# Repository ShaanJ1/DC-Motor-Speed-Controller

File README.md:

# DC-Motor-Speed-Controller
A PWM speed controller made for the 775 DC Motor, but can be used with other motors as well. It features on/off buttons, an indicator LED, and a potentiometer to control the motor's speed

I made this as Version 2 of my motor controller for my V8 Engine project, as that board failed to work entirely because of bad design.

# Bill of Materials (BOM)

| **Item Name/Purpose** | **Product Number** | **URL** | **Price** | **Quantity** | **Designator** | **Note** |
| --------------------- | ------------------ | ------- | --------: | -----------: | -------------- | -------- |
| PCB | | https://jlcpcb.com/ | $3.50 | 5 | | |
| P Channel MOSFET | SI2323CDS-T1-BE3 | https://www.digikey.com/en/products/detail/vishay-siliconix/SI2323CDS-T1-BE3/16397482 | $1.21 | 1 | Q4 | |
| Zener Diode | MMSZ5V6T1G | https://www.digikey.ca/en/products/detail/onsemi/MMSZ5V6T1G/1749053 | $0.17 | 1 | D1 | |
| NPN Transistor | MMBT2222A-TP | https://www.digikey.ca/en/products/detail/mcc-micro-commercial-components/MMBT2222A-TP/717279 | $0.24 | 2 | Q3, Q6 | |
| 6A 2920 PTC Fuse | 2920L600/16MR | https://www.digikey.ca/en/products/detail/littelfuse-inc/2920L600-16MR/14320022 | $2.20 | 2 | F1 | |
| Flywheeling Diode | MBR2045CT | https://www.digikey.ca/en/products/detail/taiwan-semiconductor-corporation/MBR2045CT/7357796 | $1.72 | 1 | D3 | |
| N Channel MOSFET | IRF3205STRLPBF | https://www.digikey.ca/en/products/detail/infineon-technologies/IRF3205STRLPBF/856540 | $3.00 | 1 | Q5 | |
| Diode | 1N4148W-13-F | https://www.digikey.ca/en/products/detail/diodes-incorporated/1N4148W-13-F/1933928 | $0.36 | 2 | D5, D6 | |
| 0.01uF 0603 Capacitor | 06035C103MAZ2A | https://www.digikey.ca/en/products/detail/kyocera-avx/06035C103MAZ2A/11250083 | $0.12 | 1 | C2 | |
| 0.1uF 0704 C0G/NP0 Capacitor | GRMJN65C1H104JE01D | https://www.digikey.ca/en/products/detail/murata-electronics/GRMJN65C1H104JE01D/19115560 | $0.37 | 1 | C1 | |
| 555 Timer | LMC555 | https://www.digikey.ca/en/products/detail/texas-instruments/LMC555CMX-NOPB/334874 | $1.15 | 1 | U1 | |
| 10k 0603 Resistor | RC0603FR-0710KL | https://www.digikey.ca/en/products/detail/yageo/RC0603FR-0710KL/726880 | $0.25 | 10 | R1, R5, R6, R8, R11 | Cheaper to get 10 resistors than only 5 |
| 4.7K 0603 Resistor | RMCF0603FT4K70 | https://www.digikey.ca/en/products/detail/stackpole-electronics-inc/RMCF0603FT4K70/1760998 | $0.10 | 1 | R2 | |
| 1K 0603 Resistor | RMCF0603FT1K00 | https://www.digikey.ca/en/products/detail/stackpole-electronics-inc/RMCF0603FT1K00/1761077 | $0.21 | 10 | R3, R4, R7, R9, R10 | Cheaper to get 10 resistors than only 5 |
| 0805 SMD LED | LTST-C171KGKT | https://www.digikey.ca/en/products/detail/liteon/LTST-C171KGKT/386799 | $0.12 | 1 | D4 | |
| 1x2 Screw Terminals | 282837-2 | https://www.digikey.ca/en/products/detail/te-connectivity-amp-connectors/282837-2/2187973 | $3.44 | 2 | J1, M1 | |

#### <ins>Totals (not including taxes or shipping)</ins>

**Total (CAD):** $17.72

**Total (USD):** $12.57

### Images
Schematic

PCB

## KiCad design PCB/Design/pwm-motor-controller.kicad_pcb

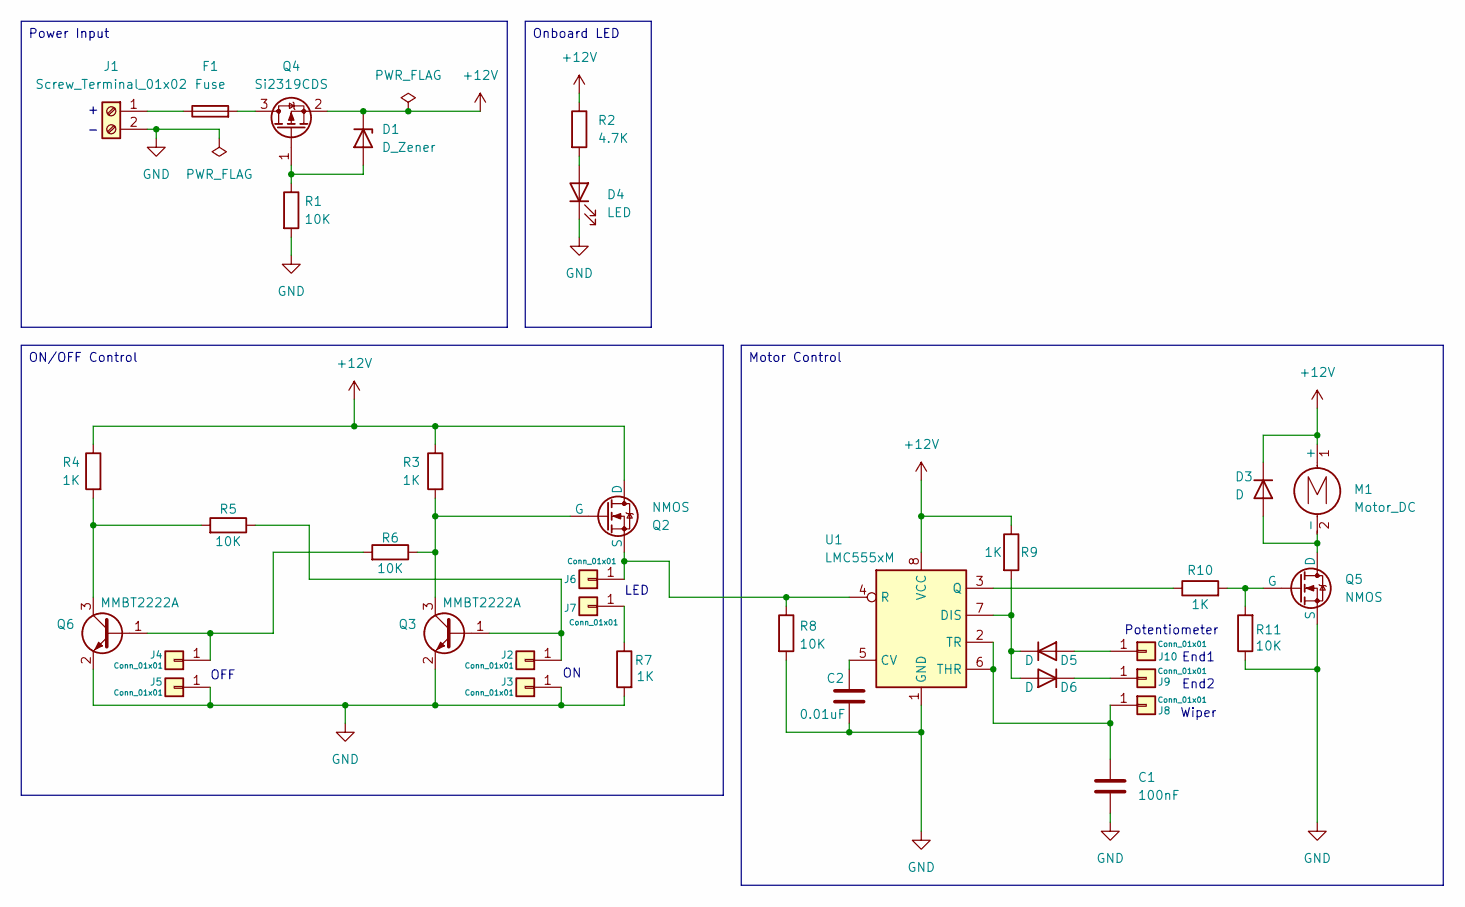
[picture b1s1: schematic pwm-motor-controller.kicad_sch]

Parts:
C1: 100nF; GRMJN65C1H104JE01D
C2: 0.01uF; C_0603_1608Metric
D1: D_Zener; D_SOD-123
D3: D; TO-220-3_Horizontal_TabDown
D4: LED; LED_0805_2012Metric_Pad1.15x1.40mm_HandSolder
D5, D6: D; Nexperia_CFP3_SOD-123W
F1: Fuse; Fuse_2920_7451Metric
J1: Screw_Terminal_01x02; TerminalBlock_Phoenix_MKDS-1,5-2-5.08_1x02_P5.08mm_Horizont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
J2, J3, J4, J5, J6, J7, J8, J9, J10: Conn_01x01; TestPoint_THTPad_2.0x2.0mm_Drill1.0mm
M1: Motor_DC; TerminalBlock_Phoenix_MKDS-1,5-2-5.08_1x02_P5.08mm_Horizont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
Q2: NMOS; SOT-23
Q3, Q6: MMBT2222A; SOT-23
Q4: Si2319CDS; SOT-23
Q5: NMOS; TO-263-2
R1, R5, R6, R8, R11: 10K; R_0603_1608Metric
R2: 4.7K; R_0603_1608Metric
R3, R4, R7, R9, R10: 1K; R_0603_1608Metric
U1: LMC555xM; SOIC-8_3.9x4.9mm_P1.27mm

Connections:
+12V: D1.1 (K), D3.1 (K), M1.1 (+), Q2.1 (D), Q4.2 (S), R2.1, R3.1, R4.1, R9.1, U1.8 (VCC)
GND: C1.2, C2.1, D4.1 (K), J1.2, J3.1, J5.1, Q3.2 (E), Q5.3 (S), Q6.2 (E), R1.2, R7.2, R8.2, R11.1, U1.1 (GND)
unnamed: D1.2 (A), Q4.1 (G), R1.1
unnamed: D3.2 (A), M1.2 (-), Q5.1 (D)
unnamed: D4.2 (A), R2.2
unnamed: D5.2 (A), J10.1
unnamed: D5.1 (K), D6.2 (A), R9.2, U1.7 (DIS)
unnamed: D6.1 (K), J9.1
unnamed: F1.1, J1.1
unnamed: J2.1, Q3.1 (B), R5.1
unnamed: J4.1, Q6.1 (B), R6.2
unnamed: J6.1, Q2.3 (S), R8.1, U1.4 (R)
unnamed: J7.1, R7.1
unnamed: C1.1, J8.1, U1.2 (TR), U1.6 (THR)
unnamed: Q2.2 (G), Q3.3 (C), R3.2, R6.1
unnamed: F1.2, Q4.3 (D)
unnamed: Q5.2 (G), R10.2, R11.2
unnamed: Q6.3 (C), R4.2, R5.2
unnamed: C2.2, U1.5 (CV)
unnamed: R10.1, U1.3 (Q)

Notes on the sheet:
LED
Potentiometer
Wiper
OFF
End2
End1
Power Input
ON/OFF Control
Onboard LED
Motor Control

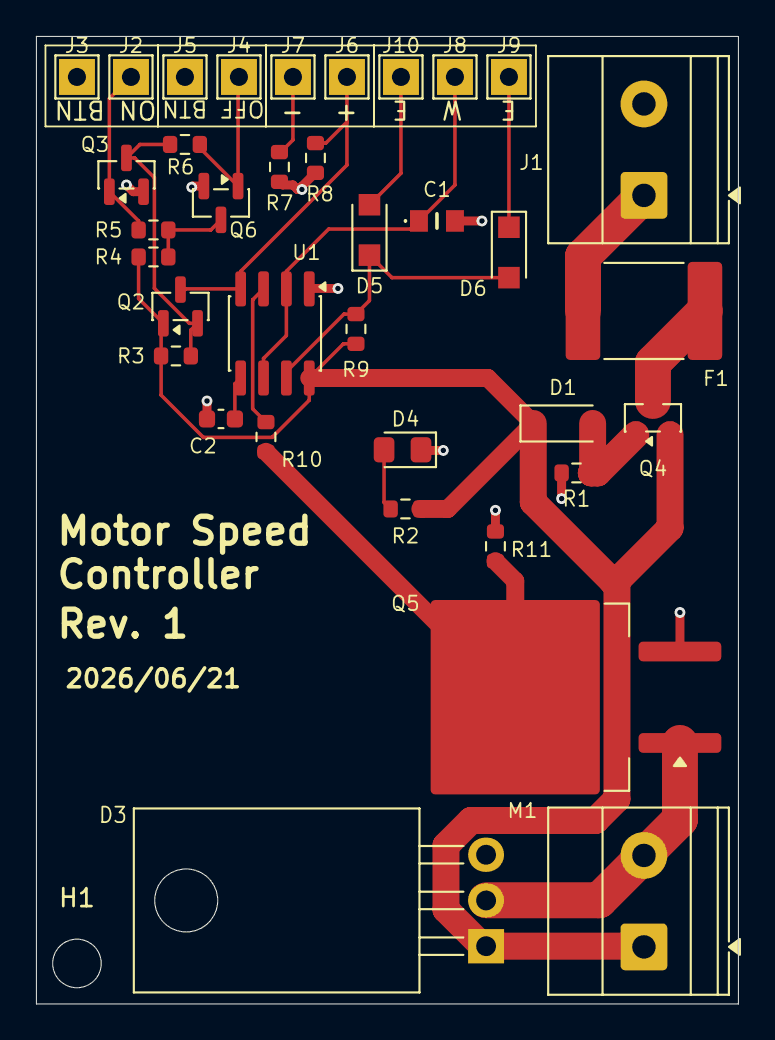
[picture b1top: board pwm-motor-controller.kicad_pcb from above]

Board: 2 copper layers, 39.0 x 53.8 mm, 37 parts (0 on the bottom side), 20 nets.

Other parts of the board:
H1: MountingHole; MountingHole_2.7mm_M2.5

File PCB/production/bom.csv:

Designator,Footprint,Quantity,Value,LCSC Part #
C1,GRMJN65C1H104JE01D,1,100nF,
C2,0603,1,0.01uF,
D1,D_SOD-123,1,D_Zener,
D3,TO-220-3_Horizontal_TabDown,1,D,
D4,0805,1,LED,
"D5, D6",Nexperia_CFP3_SOD-123W,2,D,
F1,2920,1,Fuse,
J1,"TerminalBlock_Phoenix_MKDS-1,5-2-5.08_1x02_P5.08mm_Horizontal",1,Screw_Terminal_01x02,
"J10, J2, J3, J4, J5, J6, J7, J8, J9",TestPoint_THTPad_2.0x2.0mm_Drill1.0mm,9,Conn_01x01,
M1,"TerminalBlock_Phoenix_MKDS-1,5-2-5.08_1x02_P5.08mm_Horizontal",1,Motor_DC,
Q2,SOT-23,1,NMOS,
"Q3, Q6",SOT-23,2,MMBT2222A,
Q4,SOT-23,1,Si2319CDS,
Q5,TO-263-2,1,NMOS,
"R1, R11, R5, R6, R8",0603,5,10K,
"R10, R3, R4, R7, R9",0603,5,1K,
R2,0603,1,4.7K,
U1,SOIC-8_3.9x4.9mm_P1.27mm,1,LMC555xM,

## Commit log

2026-06-17 init
2026-06-18 Update BOM
2026-06-18 Rename test.csv to bom.csv
2026-06-22 Added mounting holes
2026-06-22 Remove duplicates
